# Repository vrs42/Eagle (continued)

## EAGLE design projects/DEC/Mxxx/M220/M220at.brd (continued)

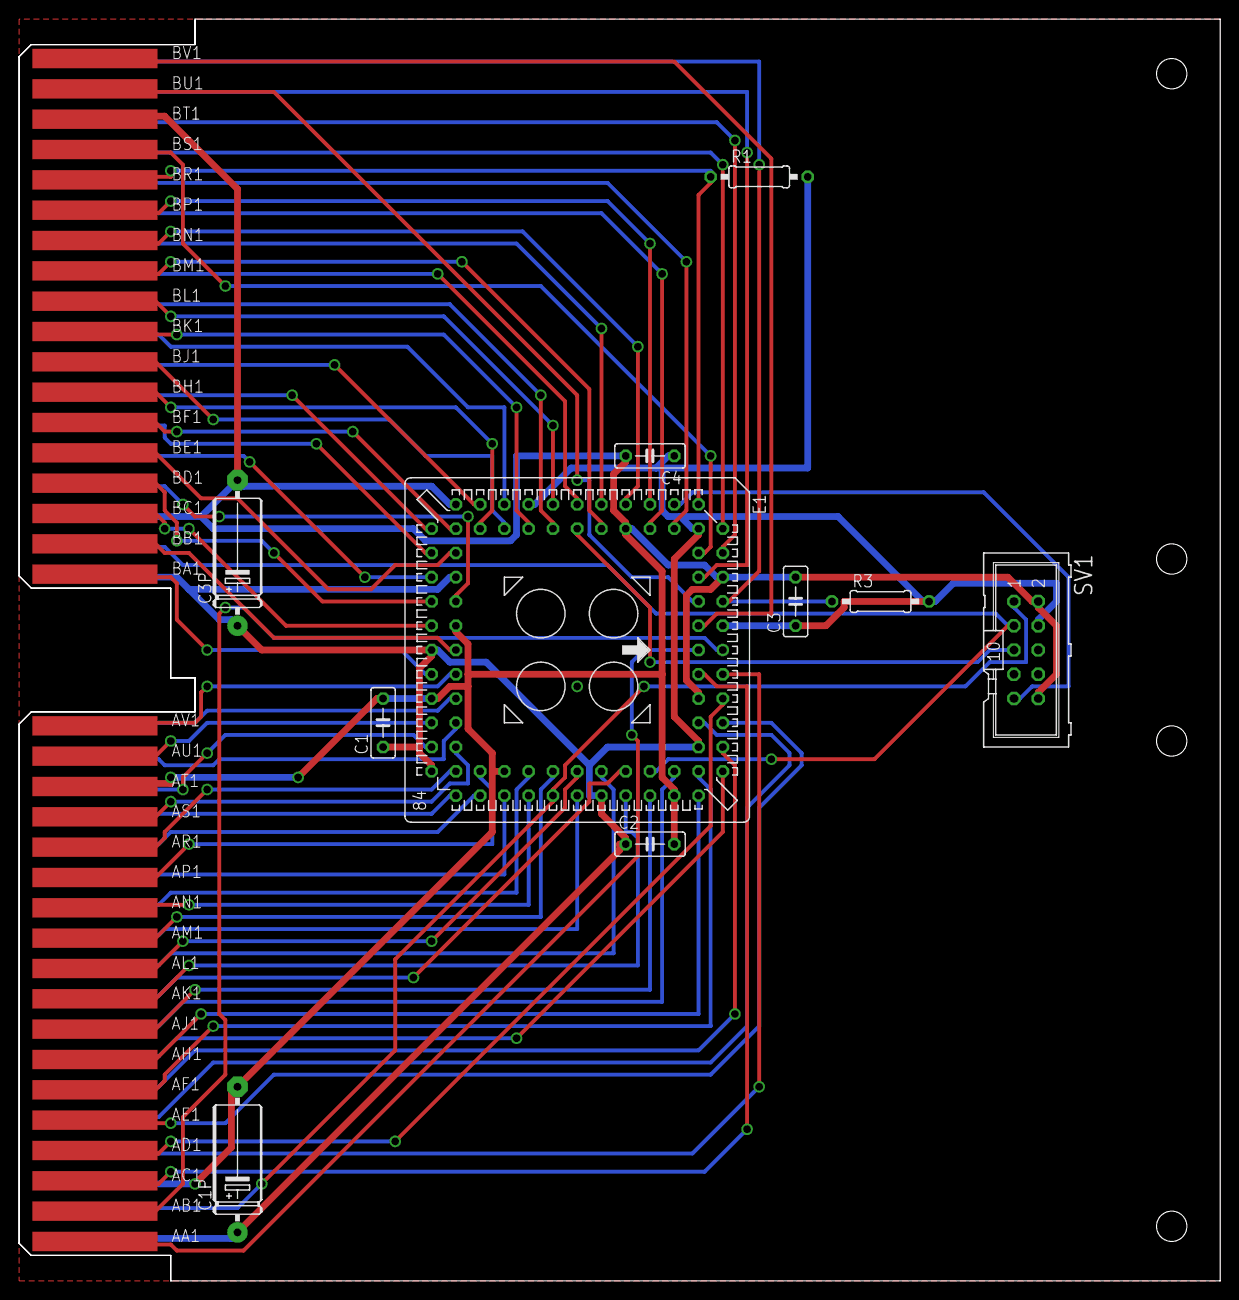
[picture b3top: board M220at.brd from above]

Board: 2 copper layers, 125.7 x 132.1 mm, 12 parts (0 on the bottom side), 70 nets.

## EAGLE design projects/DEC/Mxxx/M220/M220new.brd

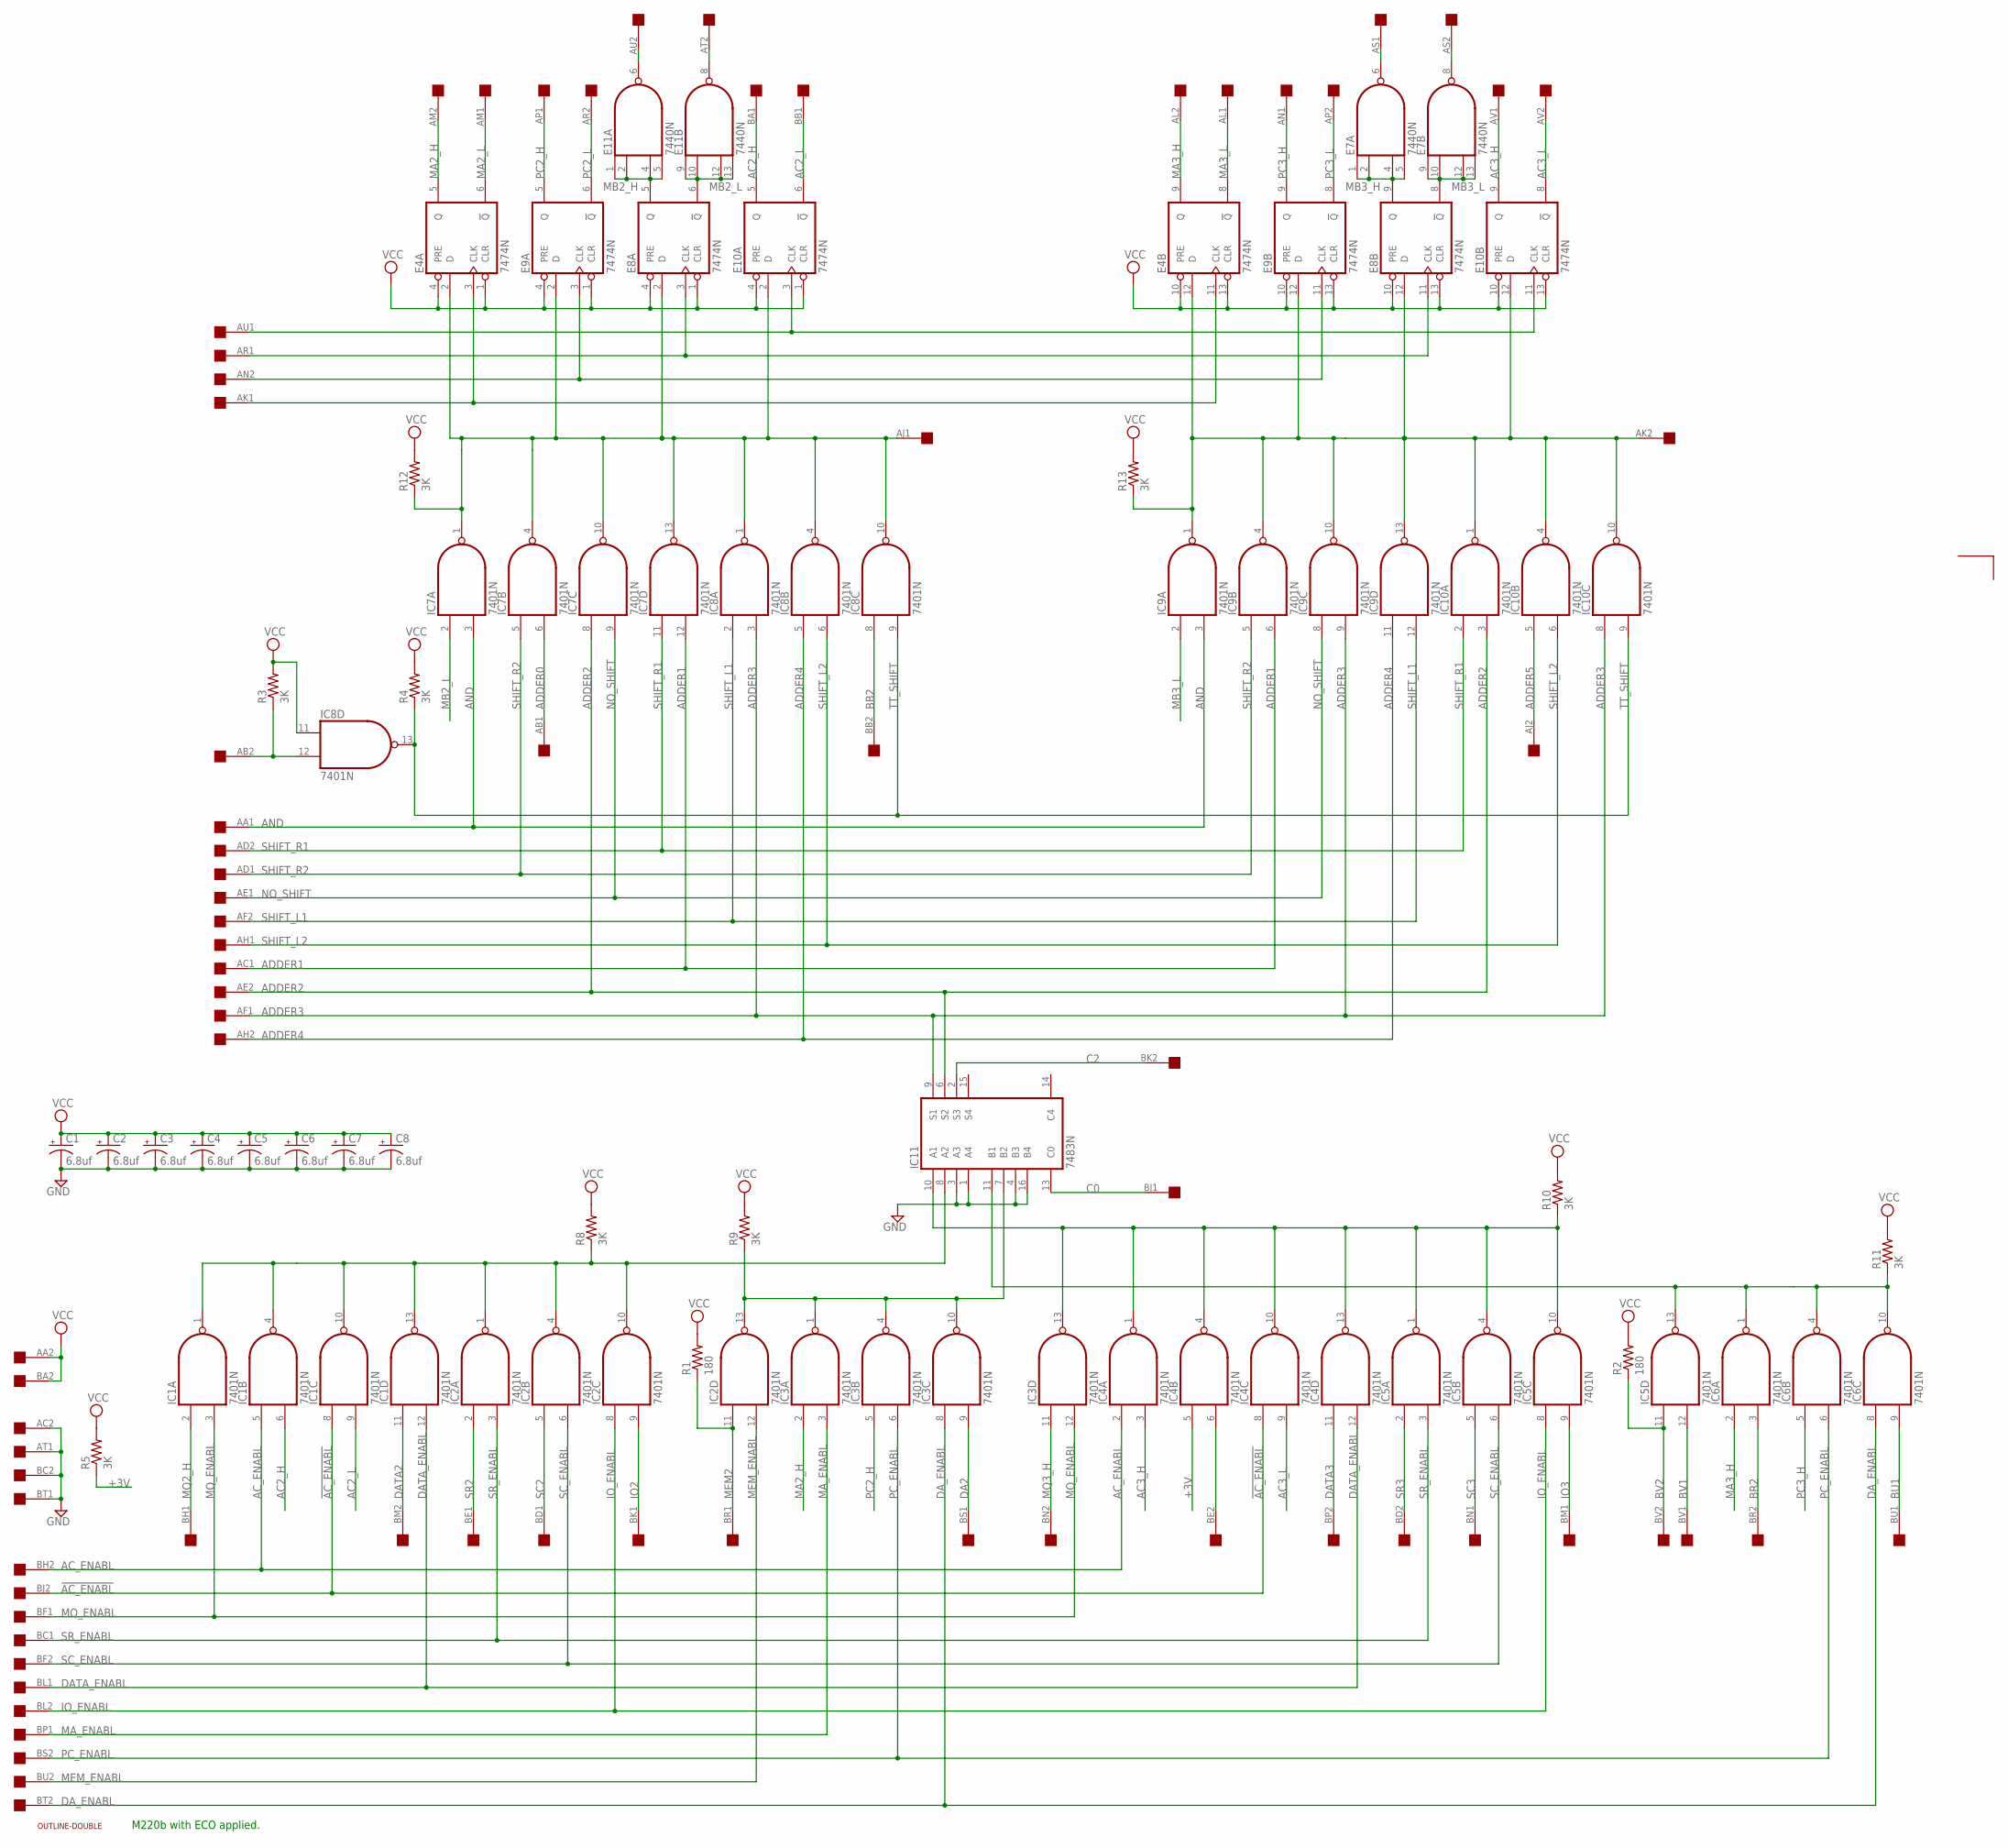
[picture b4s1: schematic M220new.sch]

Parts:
C1, C2, C3, C4, C5, C6, C7, C8: 6.8uf; E15-5
E4, E8, E9, E10: 7474N; DIL14
E7, E11: 7440N; DIL14
IC1, IC2, IC3, IC4, IC5, IC6, IC7, IC8, IC9, IC10: 7401N; DIL14
IC11: 7483N; DIL16
R1, R2: 180; 0207/10
R3, R4, R5, R8, R9, R10, R11, R12, R13: 3K; 0207/10
U$1: DOUBLE; EDGE-CON4
U$2: OUTLINE-DOUBLE; DOUBLE

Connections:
!AC_ENABL: IC1.8 (I0), IC4.8 (I0), U$1.BJ2
!TT_SHIFT: IC8.12 (I1), R3.1, U$1.AB2
+3V: IC4.5 (I0), R5.1
AC2_H: E10.5 (Q), IC1.6 (I1), U$1.BA1
AC2_L: E10.6 (!Q), IC1.9 (I1), U$1.BB1
AC3_H: E10.9 (Q), IC4.3 (I1), U$1.AV1
AC3_L: E10.8 (!Q), IC4.9 (I1), U$1.AV2
AC_ENABL: IC1.5 (I0), IC4.2 (I0), U$1.BH2
ADDER0: IC7.6 (I1), U$1.AB1
ADDER1: IC7.12 (I1), IC9.6 (I1), U$1.AC1
ADDER2: IC7.8 (I0), IC10.3 (I1), IC11.6 (S2), U$1.AE2
ADDER3: IC8.3 (I1), IC9.9 (I1), IC10.8 (I0), IC11.9 (S1), U$1.AF1
ADDER4: IC8.5 (I0), IC9.11 (I0), U$1.AH2
ADDER5: IC10.5 (I0), U$1.AJ2
AJ1: E4.2 (D), E8.2 (D), E9.2 (D), E10.2 (D), IC7.1 (O), IC7.4 (O), IC7.10 (O), IC7.13 (O), IC8.1 (O), IC8.4 (O), IC8.10 (O), R12.1, U$1.AJ1
AK1: E4.3 (CLK), E4.11 (CLK), U$1.AK1
AK2: E4.12 (D), E8.12 (D), E9.12 (D), E10.12 (D), IC9.1 (O), IC9.4 (O), IC9.10 (O), IC9.13 (O), IC10.1 (O), IC10.4 (O), IC10.10 (O), R13.1, U$1.AK2
AN2: E9.3 (CLK), E9.11 (CLK), U$1.AN2
AND: IC7.3 (I1), IC9.3 (I1), U$1.AA1
AR1: E8.3 (CLK), E8.11 (CLK), U$1.AR1
AS1: E7.6 (O), U$1.AS1
AS2: E7.8 (O), U$1.AS2
AT2: E11.8 (O), U$1.AT2
AU1: E10.3 (CLK), E10.11 (CLK), U$1.AU1
AU2: E11.6 (O), U$1.AU2
BB2: IC8.8 (I0), U$1.BB2
BE2: IC4.6 (I1), U$1.BE2
BR2: IC6.3 (I1), U$1.BR2
BU1: IC6.9 (I1), U$1.BU1
BV1: IC5.12 (I1), U$1.BV1
BV2: IC5.11 (I0), R2.1, U$1.BV2
C0: IC11.13 (C0), U$1.BJ1
C2: IC11.2 (S3), U$1.BK2
DA2: IC3.9 (I1), U$1.BS1
DATA2: IC1.11 (I0), U$1.BM2
DATA3: IC4.11 (I0), U$1.BP2
DATA_ENABL: IC1.12 (I1), IC4.12 (I1), U$1.BL1
DA_ENABL: IC3.8 (I0), IC6.8 (I0), U$1.BT2
GND: C1.-, C2.-, C3.-, C4.-, C5.-, C6.-, C7.-, C8.-, E4.7 (GND), E7.7 (GND), E8.7 (GND), E9.7 (GND), E10.7 (GND), E11.7 (GND), IC1.7 (GND), IC2.7 (GND), IC3.7 (GND), IC4.7 (GND), IC5.7 (GND), IC6.7 (GND), IC7.7 (GND), IC8.7 (GND), IC9.7 (GND), IC10.7 (GND), IC11.1 (A4), IC11.3 (A3), IC11.4 (B3), IC11.12 (GND), IC11.16 (B4), U$1.AC2, U$1.AT1, U$1.BC2, U$1.BT1
IO2: IC2.9 (I1), U$1.BK1
IO3: IC5.9 (I1), U$1.BM1
IO_ENABL: IC2.8 (I0), IC5.8 (I0), U$1.BL2
MA2_H: E4.5 (Q), IC3.2 (I0), U$1.AM2
MA2_L: E4.6 (!Q), U$1.AM1
MA3_H: E4.9 (Q), IC6.2 (I0), U$1.AL2
MA3_L: E4.8 (!Q), U$1.AL1
MA_ENABL: IC3.3 (I1), U$1.BP1
MB2_H: E8.5 (Q), E11.1 (I0), E11.2 (I1), E11.4 (I2), E11.5 (I3)
MB2_L: E8.6 (!Q), E11.9 (I0), E11.10 (I1), E11.12 (I2), E11.13 (I3), IC7.2 (I0)
MB3_H: E7.1 (I0), E7.2 (I1), E7.4 (I2), E7.5 (I3), E8.9 (Q)
MB3_L: E7.9 (I0), E7.10 (I1), E7.12 (I2), E7.13 (I3), E8.8 (!Q), IC9.2 (I0)
MEM2: IC2.11 (I0), R1.1, U$1.BR1
MEM_ENABL: IC2.12 (I1), U$1.BU2
MQ2_H: IC1.2 (I0), U$1.BH1
MQ3_H: IC3.11 (I0), U$1.BN2
MQ_ENABL: IC1.3 (I1), IC3.12 (I1), U$1.BF1
unnamed: IC1.1 (O), IC1.4 (O), IC1.10 (O), IC1.13 (O), IC2.1 (O), IC2.4 (O), IC2.10 (O), IC11.8 (A2), R8.1
unnamed: IC3.13 (O), IC4.1 (O), IC4.4 (O), IC4.10 (O), IC4.13 (O), IC5.1 (O), IC5.4 (O), IC5.10 (O), IC11.10 (A1), R10.1
unnamed: IC2.13 (O), IC3.1 (O), IC3.4 (O), IC3.10 (O), IC11.7 (B2), R9.1
unnamed: IC5.13 (O), IC6.1 (O), IC6.4 (O), IC6.10 (O), IC11.11 (B1), R11.1
NO_SHIFT: IC7.9 (I1), IC9.8 (I0), U$1.AE1
PC2_H: E9.5 (Q), IC3.5 (I0), U$1.AP1
PC2_L: E9.6 (!Q), U$1.AR2
PC3_H: E9.9 (Q), IC6.5 (I0), U$1.AN1
PC3_L: E9.8 (!Q), U$1.AP2
PC_ENABL: IC3.6 (I1), IC6.6 (I1), U$1.BS2
SC2: IC2.5 (I0), U$1.BD1
SC3: IC5.5 (I0), U$1.BN1
SC_ENABL: IC2.6 (I1), IC5.6 (I1), U$1.BF2
SHIFT_L1: IC8.2 (I0), IC9.12 (I1), U$1.AF2
SHIFT_L2: IC8.6 (I1), IC10.6 (I1), U$1.AH1
SHIFT_R1: IC7.11 (I0), IC10.2 (I0), U$1.AD2
SHIFT_R2: IC7.5 (I0), IC9.5 (I0), U$1.AD1
SR2: IC2.2 (I0), U$1.BE1
SR3: IC5.2 (I0), U$1.BD2
SR_ENABL: IC2.3 (I1), IC5.3 (I1), U$1.BC1
TT_SHIFT: IC8.9 (I1), IC8.13 (O), IC10.9 (I1), R4.1
VCC: C1.+, C2.+, C3.+, C4.+, C5.+, C6.+, C7.+, C8.+, E4.1 (CLR), E4.4 (PRE), E4.10 (PRE), E4.13 (CLR), E4.14 (VCC), E7.14 (VCC), E8.1 (CLR), E8.4 (PRE), E8.10 (PRE), E8.13 (CLR), E8.14 (VCC), E9.1 (CLR), E9.4 (PRE), E9.10 (PRE), E9.13 (CLR), E9.14 (VCC), E10.1 (CLR), E10.4 (PRE), E10.10 (PRE), E10.13 (CLR), E10.14 (VCC), E11.14 (VCC), IC1.14 (VCC), IC2.14 (VCC), IC3.14 (VCC), IC4.14 (VCC), IC5.14 (VCC), IC6.14 (VCC), IC7.14 (VCC), IC8.11 (I0), IC8.14 (VCC), IC9.14 (VCC), IC10.14 (VCC), IC11.5 (VCC), R1.2, R2.2, R3.2, R4.2, R5.2, R8.2, R9.2, R10.2, R11.2, R12.2, R13.2, U$1.AA2, U$1.BA2

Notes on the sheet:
M220b with ECO applied.

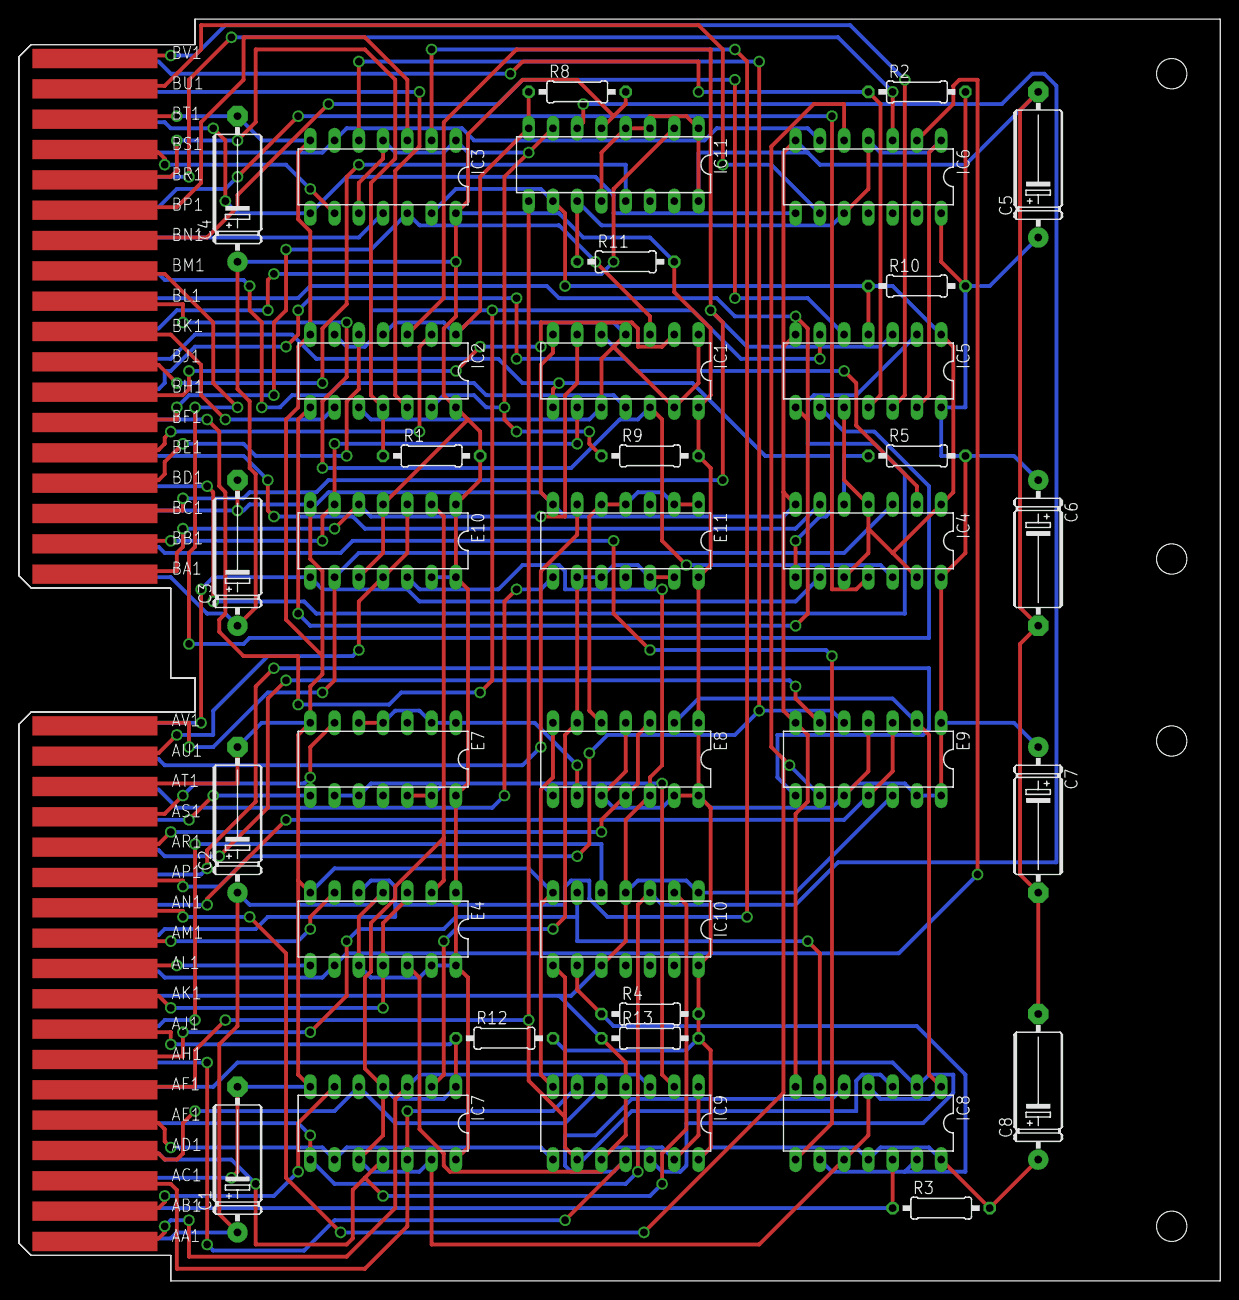
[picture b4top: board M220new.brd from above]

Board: 2 copper layers, 125.7 x 132.1 mm, 38 parts (0 on the bottom side), 78 nets.

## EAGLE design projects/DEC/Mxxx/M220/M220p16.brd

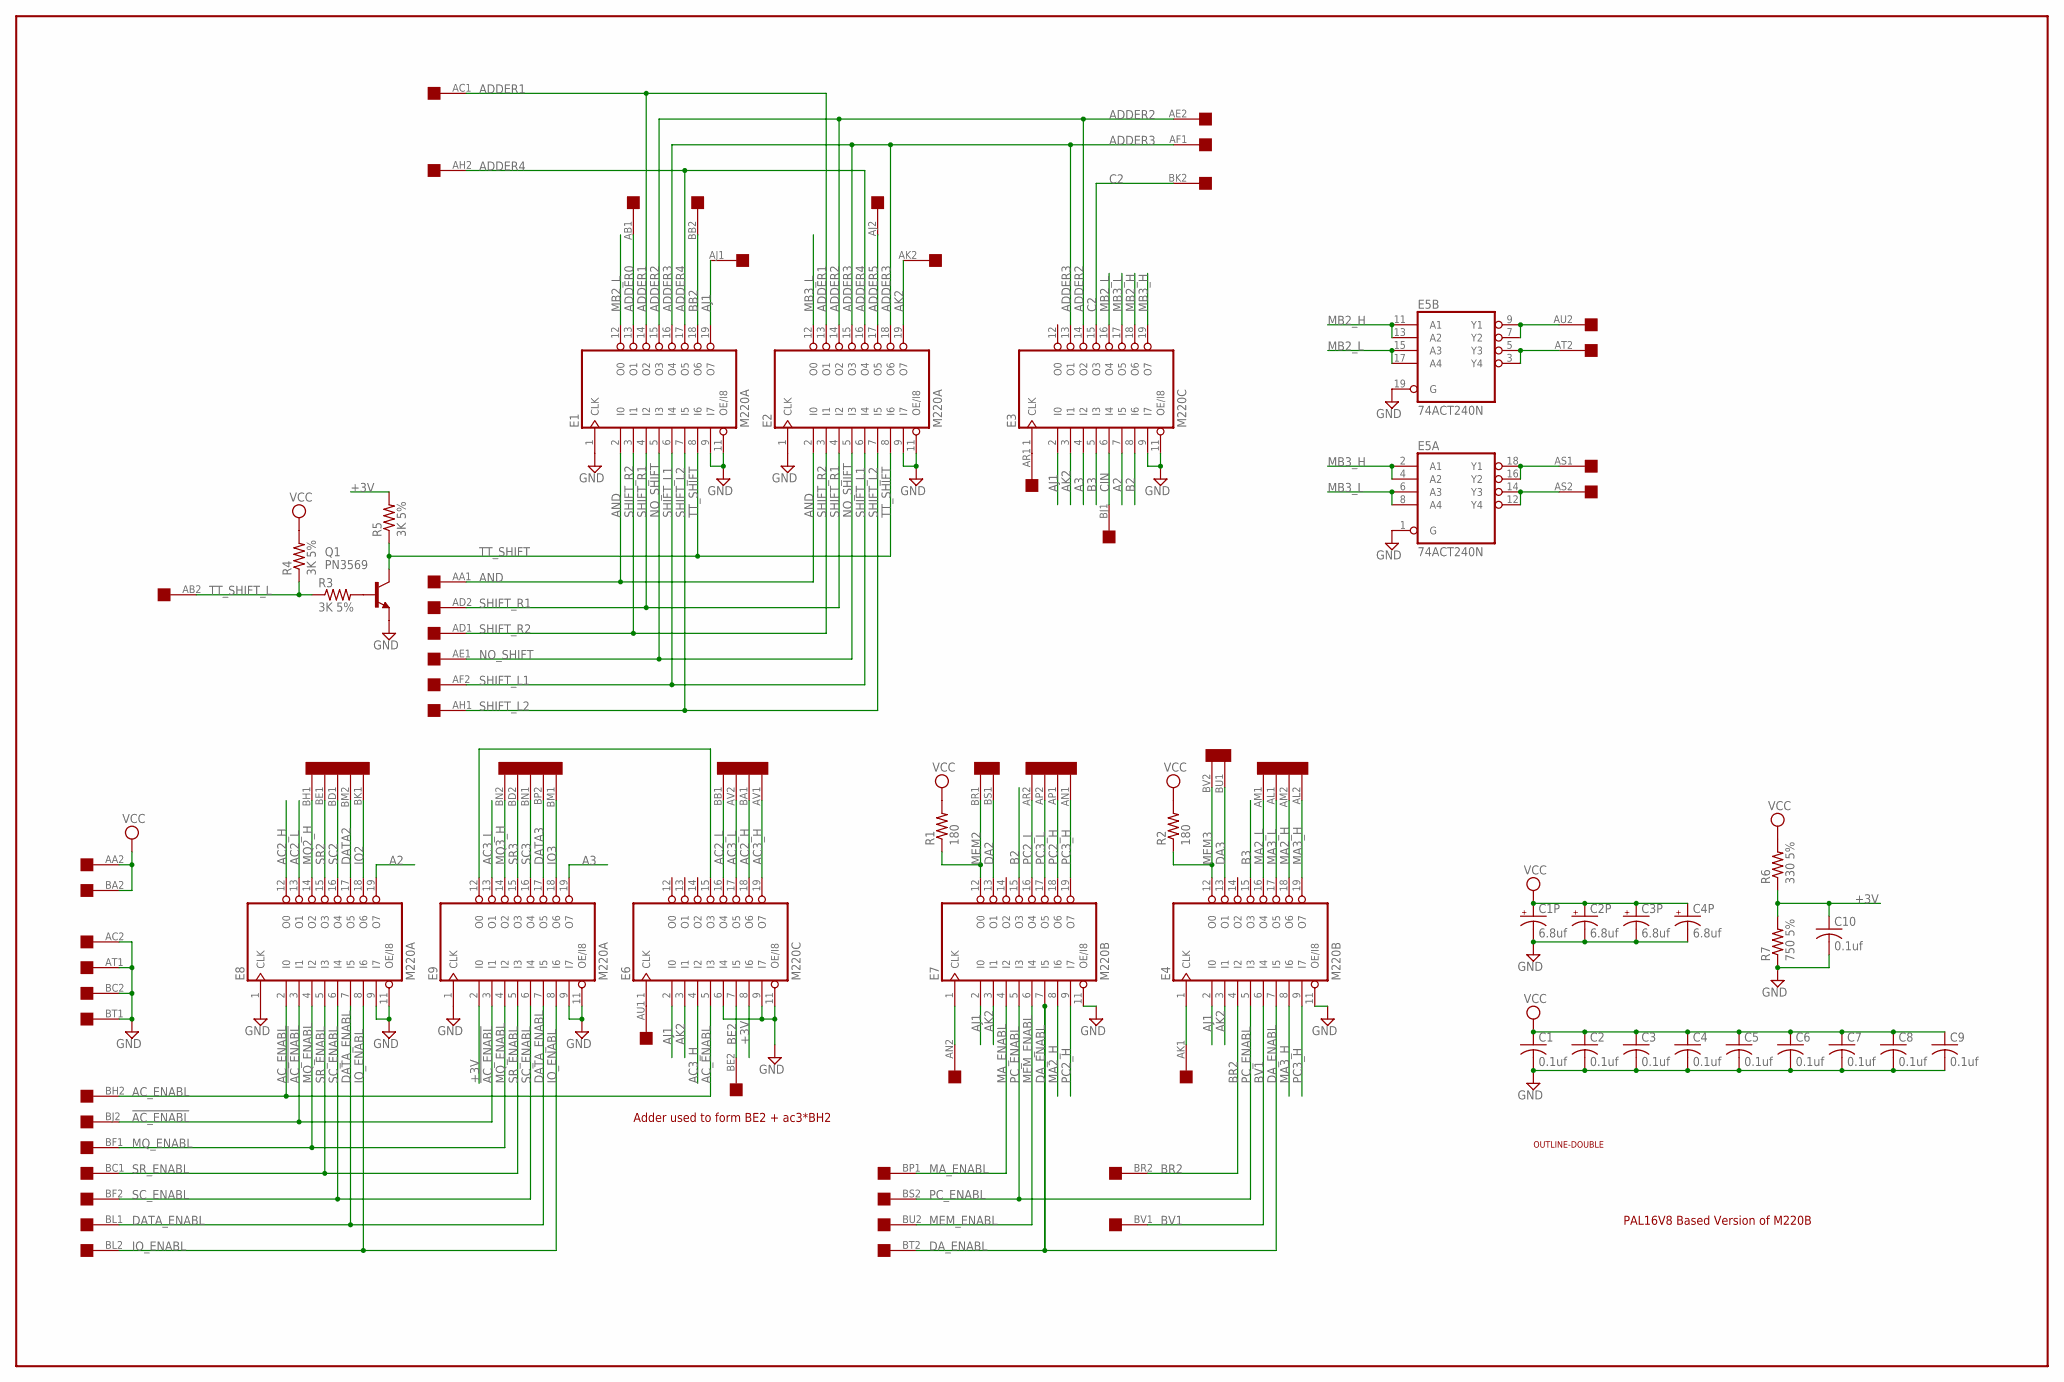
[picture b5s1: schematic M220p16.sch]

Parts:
C1, C2, C3, C4, C5, C6, C7, C8, C9, C10: 0.1uf; C050-025X075
C1P, C2P, C3P, C4P: 6.8uf; E15-5
E1, E2, E8, E9: M220A; DIL20
E3, E6: M220C; DIL20
E4, E7: M220B; DIL20
E5: 74ACT240N; DIL20
Q1: PN3569; TO5
R1, R2: 180; 0207/10
R3, R4, R5: 3K 5%; 0207/10
R6: 330 5%; 0207/10
R7: 750 5%; 0207/10
U$1: DOUBLE; EDGE-CON4
U$2: OUTLINE-DOUBLE; DOUBLE

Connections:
!AC_ENABL: E8.3 (I1), E9.3 (I1), U$1.BJ2
+3V: C10.1, E6.8 (I6), E9.2 (I0), R5.2, R6.1, R7.2
A2: E3.7 (I5), E8.19 (O7)
A3: E3.4 (I2), E9.19 (O7)
AC2_H: E6.18 (O6), E8.12 (O0), U$1.BA1
AC2_L: E6.16 (O4), E8.13 (O1), U$1.BB1
AC3_H: E6.4 (I2), E6.19 (O7), U$1.AV1
AC3_L: E6.17 (O5), E9.13 (O1), U$1.AV2
AC_ENABL: E6.5 (I3), E8.2 (I0), U$1.BH2
ADDER0: E1.13 (O1), U$1.AB1
ADDER1: E1.14 (O2), E2.13 (O1), U$1.AC1
ADDER2: E1.15 (O3), E2.14 (O2), E3.14 (O2), U$1.AE2
ADDER3: E1.16 (O4), E2.15 (O3), E2.18 (O6), E3.13 (O1), U$1.AF1
ADDER4: E1.17 (O5), E2.16 (O4), U$1.AH2
ADDER5: E2.17 (O5), U$1.AJ2
AJ1: E1.19 (O7), E3.2 (I0), E4.2 (I0), E6.2 (I0), E7.2 (I0), U$1.AJ1
AK2: E2.19 (O7), E3.3 (I1), E4.3 (I1), E6.3 (I1), E7.3 (I1), U$1.AK2
AND: E1.2 (I0), E2.2 (I0), U$1.AA1
B2: E3.8 (I6), E7.15 (O3)
B3: E3.5 (I3), E4.15 (O3)
BB2: E1.18 (O6), U$1.BB2
BE2: E6.7 (I5), U$1.BE2
BR2: E4.4 (I2), U$1.BR2
BV1: E4.6 (I4), U$1.BV1
C2: E3.15 (O3), U$1.BK2
CIN: E3.6 (I4), U$1.BJ1
DA2: E7.13 (O1), U$1.BS1
DA3: E4.13 (O1), U$1.BU1
DATA2: E8.17 (O5), U$1.BM2
DATA3: E9.17 (O5), U$1.BP2
DATA_ENABL: E8.7 (I5), E9.7 (I5), U$1.BL1
DA_ENABL: E4.7 (I5), E7.7 (I5), U$1.BT2
GND: C1.2, C1P.-, C2.2, C2P.-, C3.2, C3P.-, C4.2, C4P.-, C5.2, C6.2, C7.2, C8.2, C9.2, C10.2, E1.1 (CLK), E1.9 (I7), E1.10 (GND), E1.11 (OE/I8), E2.1 (CLK), E2.9 (I7), E2.10 (GND), E2.11 (OE/I8), E3.9 (I7), E3.10 (GND), E3.11 (OE/I8), E4.10 (GND), E4.11 (OE/I8), E5.1 (G), E5.10 (GND), E5.19 (G), E6.6 (I4), E6.9 (I7), E6.10 (GND), E6.11 (OE/I8), E7.10 (GND), E7.11 (OE/I8), E8.1 (CLK), E8.9 (I7), E8.10 (GND), E8.11 (OE/I8), E9.1 (CLK), E9.9 (I7), E9.10 (GND), E9.11 (OE/I8), Q1.1 (E), R7.1, U$1.AC2, U$1.AT1, U$1.BC2, U$1.BT1
IO2: E8.18 (O6), U$1.BK1
IO3: E9.18 (O6), U$1.BM1
IO_ENABL: E8.8 (I6), E9.8 (I6), U$1.BL2
MA2_H: E4.18 (O6), E7.8 (I6), U$1.AM2
MA2_L: E4.16 (O4), U$1.AM1
MA3_H: E4.8 (I6), E4.19 (O7), U$1.AL2
MA3_L: E4.17 (O5), U$1.AL1
MA_ENABL: E7.4 (I2), U$1.BP1
MB2_H: E3.18 (O6), E5.11 (A1), E5.13 (A2)
MB2_L: E1.12 (O0), E3.16 (O4), E5.15 (A3), E5.17 (A4)
MB3_H: E3.19 (O7), E5.2 (A1), E5.4 (A2)
MB3_L: E2.12 (O0), E3.17 (O5), E5.6 (A3), E5.8 (A4)
MEM2: E7.12 (O0), R1.1, U$1.BR1
MEM3: E4.12 (O0), R2.1, U$1.BV2
MEM_ENABL: E7.6 (I4), U$1.BU2
MQ2_H: E8.14 (O2), U$1.BH1
MQ3_H: E9.14 (O2), U$1.BN2
MQ_ENABL: E8.4 (I2), E9.4 (I2), U$1.BF1
unnamed: E7.1 (CLK), U$1.AN2
unnamed: E4.1 (CLK), U$1.AK1
unnamed: E3.1 (CLK), U$1.AR1
unnamed: E6.1 (CLK), U$1.AU1
unnamed: E6.15 (O3), E9.12 (O0)
unnamed: E5.12 (Y4), E5.14 (Y3), U$1.AS2
unnamed: E5.16 (Y2), E5.18 (Y1), U$1.AS1
unnamed: E5.3 (Y4), E5.5 (Y3), U$1.AT2
unnamed: E5.7 (Y2), E5.9 (Y1), U$1.AU2
unnamed: Q1.2 (B), R3.2
NO_SHIFT: E1.5 (I3), E2.5 (I3), U$1.AE1
PC2_H: E7.9 (I7), E7.18 (O6), U$1.AP1
PC2_L: E7.16 (O4), U$1.AR2
PC3_H: E4.9 (I7), E7.19 (O7), U$1.AN1
PC3_L: E7.17 (O5), U$1.AP2
PC_ENABL: E4.5 (I3), E7.5 (I3), U$1.BS2
SC2: E8.16 (O4), U$1.BD1
SC3: E9.16 (O4), U$1.BN1
SC_ENABL: E8.6 (I4), E9.6 (I4), U$1.BF2
SHIFT_L1: E1.6 (I4), E2.6 (I4), U$1.AF2
SHIFT_L2: E1.7 (I5), E2.7 (I5), U$1.AH1
SHIFT_R1: E1.4 (I2), E2.4 (I2), U$1.AD2
SHIFT_R2: E1.3 (I1), E2.3 (I1), U$1.AD1
SR2: E8.15 (O3), U$1.BE1
SR3: E9.15 (O3), U$1.BD2
SR_ENABL: E8.5 (I3), E9.5 (I3), U$1.BC1
TT_SHIFT: E1.8 (I6), E2.8 (I6), Q1.3 (C), R5.1
TT_SHIFT_L: R3.1, R4.1, U$1.AB2
VCC: C1.1, C1P.+, C2.1, C2P.+, C3.1, C3P.+, C4.1, C4P.+, C5.1, C6.1, C7.1, C8.1, C9.1, E1.20 (VCC), E2.20 (VCC), E3.20 (VCC), E4.20 (VCC), E5.20 (VCC), E6.20 (VCC), E7.20 (VCC), E8.20 (VCC), E9.20 (VCC), R1.2, R2.2, R4.2, R6.2, U$1.AA2, U$1.BA2

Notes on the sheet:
PAL16V8 Based Version of M220B
Adder used to form BE2 + ac3*BH2

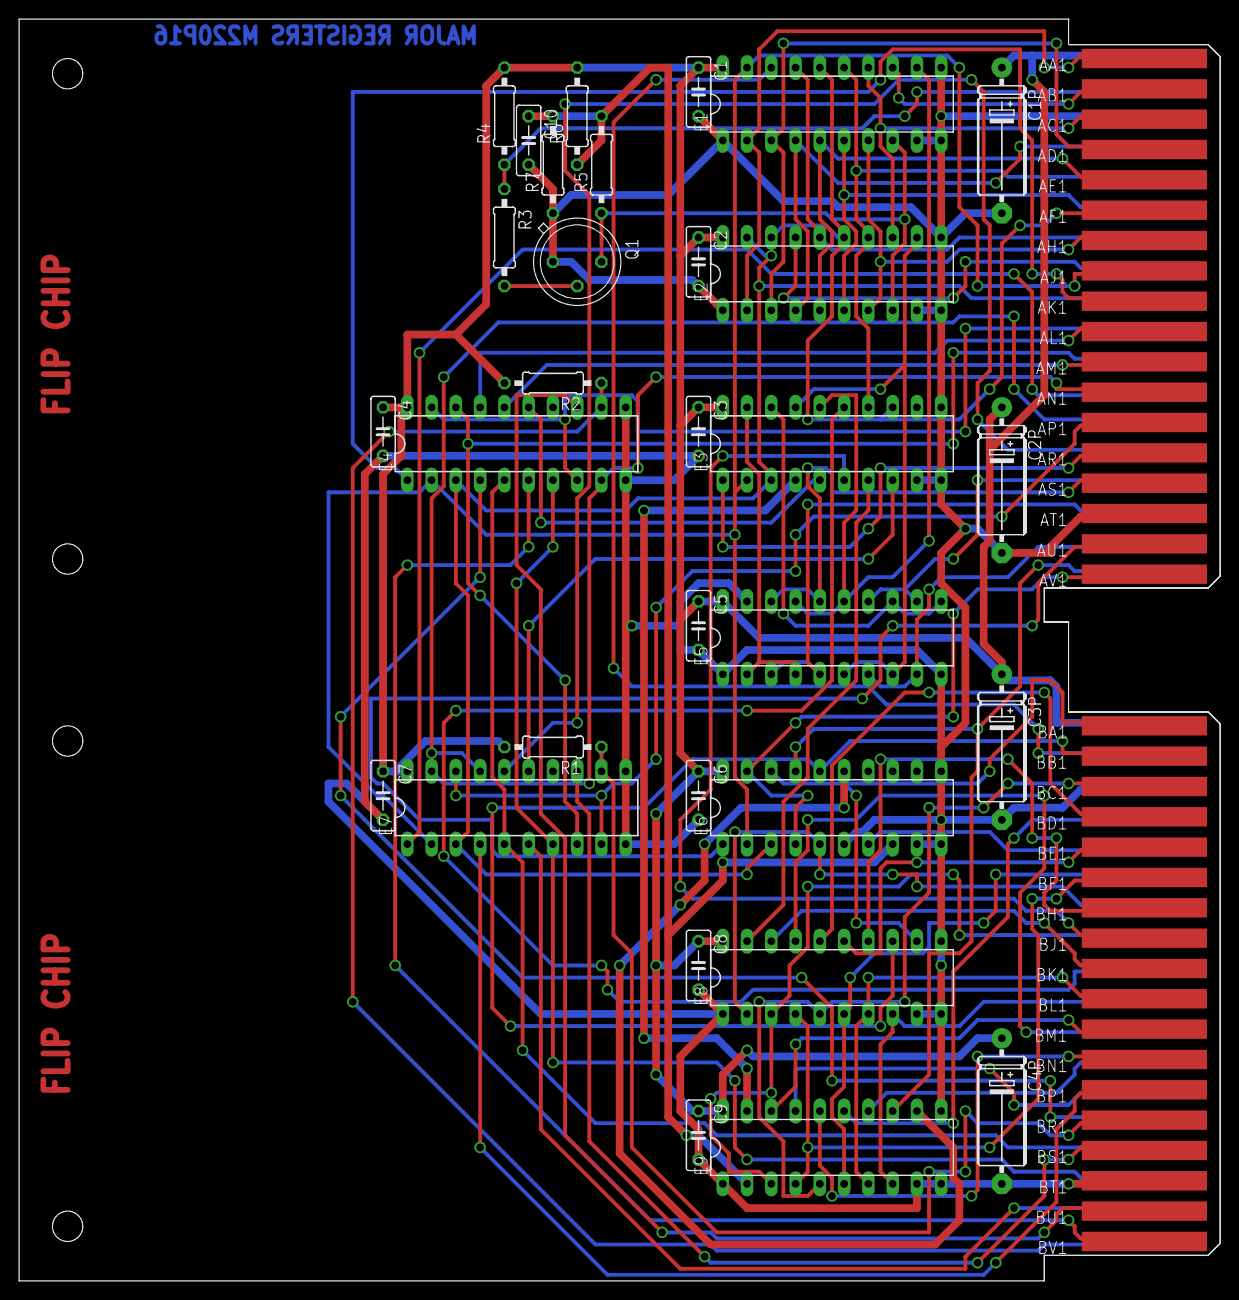
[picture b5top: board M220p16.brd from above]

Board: 2 copper layers, 125.7 x 132.1 mm, 35 parts (0 on the bottom side), 80 nets.

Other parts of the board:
U$3, U$4: FLIPCHIP
